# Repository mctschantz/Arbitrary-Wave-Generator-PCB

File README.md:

# Arbitrary-Wave-Generator-PCB
First pass at rgco's Instructable.  Board includes stubs to fit in with wolf2018's "Poor Man's..." Instructable.  Sent to JLCPCB 20SEP22.

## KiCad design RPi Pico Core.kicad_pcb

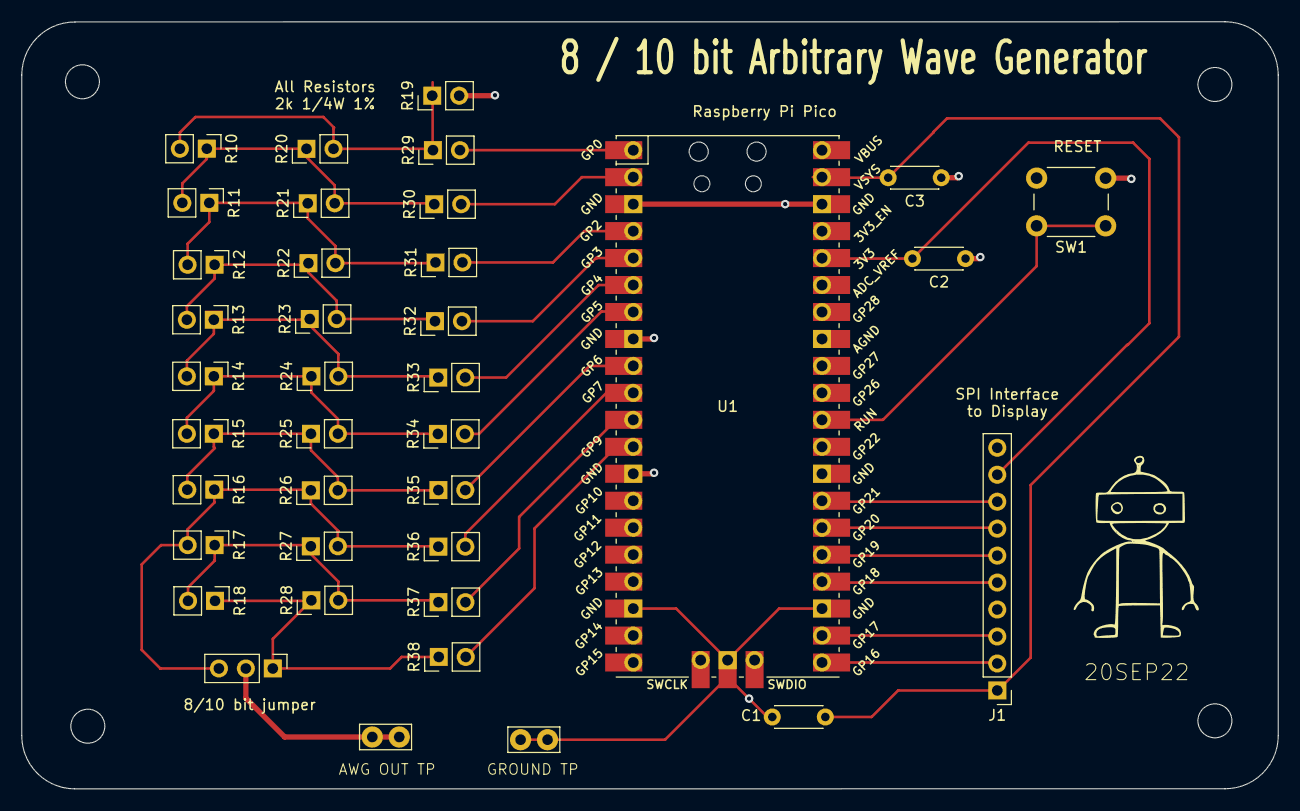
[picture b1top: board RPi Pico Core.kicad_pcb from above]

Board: 2 copper layers, 118.4 x 72.3 mm, 42 parts (0 on the bottom side), 31 nets.

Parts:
C1, C2, C3: 100 nF; C_Disc_D4.3mm_W1.9mm_P5.00mm
H1, H2, H3, H4: MountingHole; MountingHole_3.2mm_M3
J1: SPI Interface to Display; PinHeader_1x10_P2.54mm_Vertical
J2: 8/10 bit jumper; PinHeader_1x03_P2.54mm_Vertical
R10, R11, R12, R13, R14, R15, R16, R17, R18, R19, R20, R21, R22, R23, R24, R25, R26, R27, R28, R29, R30, R31, R32, R33, R34, R35, R36, R37, R38: 2k; PinHeader_1x02_P2.54mm_Vertical
SW1: RESET; SW_PUSH_6mm_H4.3mm
TP1: AWG OUT TP; TestPoint_Bridge_Pitch2.54mm_Drill1.0mm
TP2: GROUND TP; TestPoint_Bridge_Pitch2.54mm_Drill1.0mm
U1: Raspberry Pi Pico; RPi_Pico_SMD_TH

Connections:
+3.3V: C2.2, J1.9, U1.36 (3V3)
+5V: C1.2, C3.2, J1.1, U1.39 (VSYS)
GND: C1.1, C2.1, C3.1, J1.4, R19.2, SW1.2 (B), TP2.1, U1.3 (GND), U1.8 (GND), U1.13 (GND), U1.18 (GND), U1.23 (GND), U1.28 (GND), U1.38 (GND), U1.42 (GND)
unnamed: J1.2, U1.21 (GPIO16)
unnamed: J1.3, U1.22 (GPIO17)
unnamed: J1.5, U1.24 (GPIO18)
unnamed: J1.6, U1.25 (GPIO19)
unnamed: J1.7, U1.26 (GPIO20)
unnamed: J1.8, U1.27 (GPIO21)
unnamed: J2.1, R18.1, R28.1, R38.1
unnamed: J2.2, TP1.1
unnamed: J2.3, R16.1, R17.2, R26.1, R27.2, R36.1
unnamed: R10.1, R11.2, R20.1, R21.2, R30.1
unnamed: R10.2, R19.1, R20.2, R29.1
unnamed: R11.1, R12.2, R21.1, R22.2, R31.1
unnamed: R12.1, R13.2, R22.1, R23.2, R32.1
unnamed: R13.1, R14.2, R23.1, R24.2, R33.1
unnamed: R14.1, R15.2, R24.1, R25.2, R34.1
unnamed: R15.1, R16.2, R25.1, R26.2, R35.1
unnamed: R17.1, R18.2, R27.1, R28.2, R37.1
unnamed: R29.2, U1.1 (GPIO0)
unnamed: R30.2, U1.2 (GPIO1)
unnamed: R31.2, U1.4 (GPIO2)
unnamed: R32.2, U1.5 (GPIO3)
unnamed: R33.2, U1.6 (GPIO4)
unnamed: R34.2, U1.7 (GPIO5)
unnamed: R35.2, U1.9 (GPIO6)
unnamed: R36.2, U1.10 (GPIO7)
unnamed: R37.2, U1.11 (GPIO8)
unnamed: R38.2, U1.12 (GPIO9)
unnamed: SW1.1 (A), U1.30 (RUN)

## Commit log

2022-09-21 Initial AWG Schematic & PCB files
    20SEP22 - Ordered pcbs from JLCPCB
